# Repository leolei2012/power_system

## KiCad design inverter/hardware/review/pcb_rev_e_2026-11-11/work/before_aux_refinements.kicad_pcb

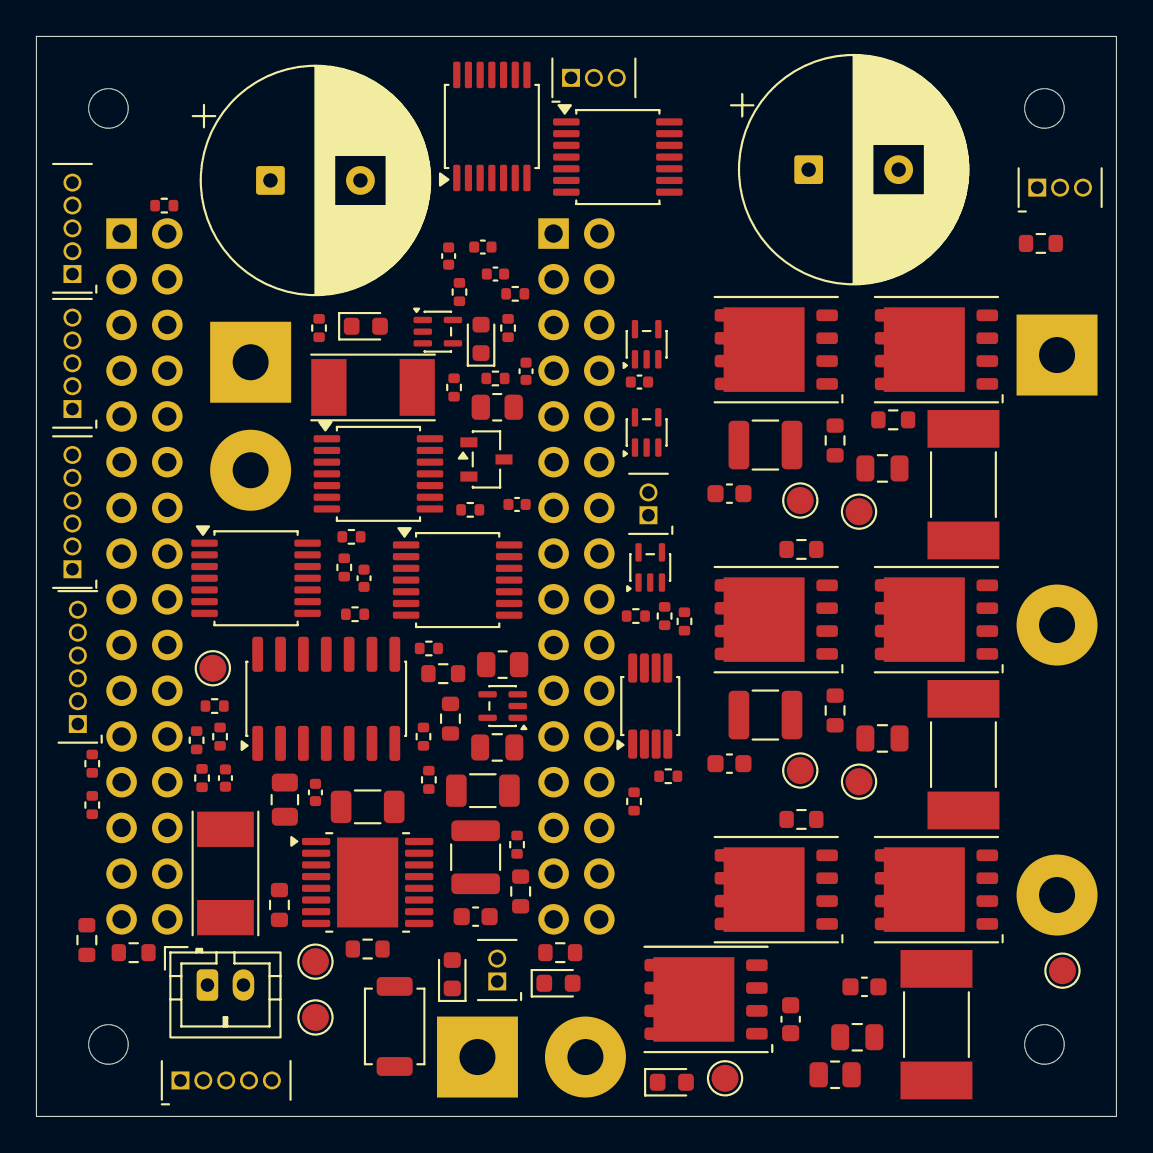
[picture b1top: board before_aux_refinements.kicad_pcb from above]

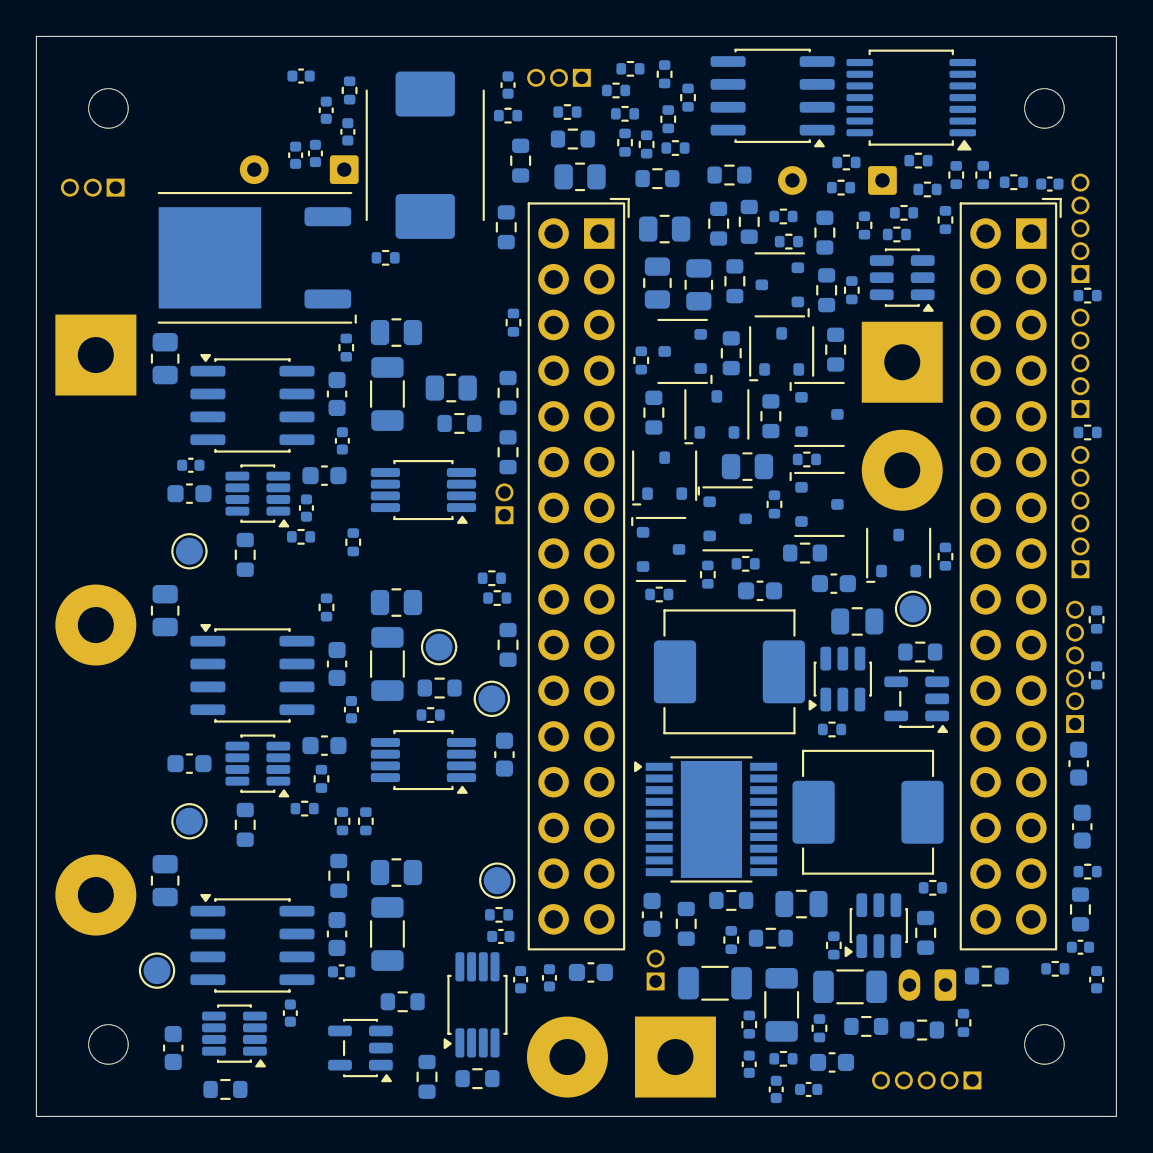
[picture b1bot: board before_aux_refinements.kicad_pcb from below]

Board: 6 copper layers, 60.0 x 60.0 mm, 321 parts (194 on the bottom side), 220 nets, no tracks yet.

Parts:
C1: 1u; C_0805_2012Metric
C2: 22n; C_0603_1608Metric
C3, C6, C11: 10u; C_1206_3216Metric
C4, C5, C9, C12, C24, C26, C28, C30, C32, C34, C36, C37, C38, C39, C51, C52, C53: 100n; C_0603_1608Metric
C7: 470n; C_0805_2012Metric
C8: 22u; C_1210_3225Metric
C10, C27, C31, C35: 4.7u; C_0805_2012Metric
C13, C14: 22u; C_1206_3216Metric
C15, C23: 1u; C_0603_1608Metric
C16: 2.2u; C_0603_1608Metric
C17, C40, C41, C43, C45, C47, C49, C54, C56, C57, C58, C59, C60, C61, C62, C82: 100n; C_0402_1005Metric
C18: 10u; C_0805_2012Metric
C19, C20: 220u / 100V; CP_Radial_D12.5mm_H25mm_P5.00mm
C21, C22: 2.2u / 100V X7R; C_1210_3225Metric
C25, C29, C33: 2.2u; C_1206_3216Metric
C42: 100p; C_0402_1005Metric
C44, C46, C48, C69, C70, C71, C72, C73, C74, C75, C76: 1n; C_0402_1005Metric
C50, C55: 10n; C_0402_1005Metric
D1: MBRD20150CT-13; Diodes_MBRD20150CT_TO252_Recommended
D2: SMCJ60CA / CANDIDATE DNP; SMC_DO-214AB_Bidirectional
D3: PWR; LED_0603_1608Metric
D4: LED_RUN; LED_0603_1608Metric
D5: LED_FAULT; LED_0603_1608Metric
D6: LED_COMM; LED_0603_1608Metric
D7: LED_AUX; LED_0603_1608Metric
D201, D202, D203, D204, D205, D206, D207, D208, D209, D210: BAT54S,215; Nexperia_SOT23_Reflow_Pad0.70x0.60mm
F1: 0476015.MRSN; Littelfuse_NANO2_451_476_Pad1.96x3.15mm_Gap2.95mm
F2: 0451002.MRL; Littelfuse_NANO2_451_476_Pad1.96x3.15mm_Gap2.95mm
H1, H2, H3, H4: MountingHole_2.2mm_M2
J2: AUX: +12..24V / GND; JST_PH_B2B-PH-K_1x02_P2.00mm_Vertical
J3: DC INPUT: + / -; WireSolder_2P_P6.00mm_D2.00mm
J4: RAW PWM: U / V / W; WireSolder_3P_P15.00mm_D2.00mm
J5: BRAKE POWER: BR+ / BR_SW; WireSolder_2P_P6.00mm_D2.00mm
J7: OPTIONAL SENSOR 5V / GND; HCTL_PZ127_1x02_P1.27mm_Drill0.70mm
J8: EXTERNAL 10k NTC; HCTL_PZ127_1x02_P1.27mm_Drill0.70mm
J9: ENC_A: PWR GND A B Z; HCTL_PZ127_1x05_P1.27mm_Drill0.70mm
J10: ENC_B: PWR GND A B Z; HCTL_PZ127_1x05_P1.27mm_Drill0.70mm
J11: SPI_A: PWR GND SCK MOSI MISO CS; HCTL_PZ127_1x06_P1.27mm_Drill0.70mm
J12: SPI_B: PWR GND SCK MOSI MISO CS; HCTL_PZ127_1x06_P1.27mm_Drill0.70mm
J13: SWD: VTREF IO CLK GND NRST; HCTL_PZ127_1x05_P1.27mm_Drill0.70mm
J14: TTL: TX RX GND; HCTL_PZ127_1x03_P1.27mm_Drill0.70mm
J15: CAN: H L GND; HCTL_PZ127_1x03_P1.27mm_Drill0.70mm
J101, J102: PM254V-12-32-H85; XFCN_PM254V-12-32-H85_2x16_P2.54mm_Vertical_Drill1.02mm
L1, L2: 4.7uH; L_Sunlord_MWSA0603S
Q1, Q2, Q3, Q4, Q5, Q6, Q7: BSC110N15NS5; Infineon_BSC110N15NS5_PG-TDSON8_8PhysicalPins
Q8: MMBT3904LT1G; onsemi_SOT-23_CASE318_Recommended
R1: 78.7k; R_0603_1608Metric
R2, R4, R7, R10, R11, R15, R16, R18, R21, R22, R23, R24, R27, R28, R29, R30, R33, R34, R35, R36, R50, R51, R55, R56, R60, R61, R65, R66, R209: 10k; R_0603_1608Metric
R3: 221k; R_0603_1608Metric
R5: 402k; R_0603_1608Metric
R6: 7.87k; R_0603_1608Metric
R8, R9: 100k; R_0603_1608Metric
R12: 20k; R_0603_1608Metric
R13, R40, R41, R44, R45, R70, R72, R73, R74, R76, R77, R78, R79, R80, R81, R82, R95, R97, R99, R102, R104, R106, R112, R118, R125, R128, R143, R160: 10k; R_0402_1005Metric
R14: 49.9k; R_0603_1608Metric
R17, R19, R20, R25, R26, R31, R32: 15; R_0805_2012Metric
R37, R38, R39: 47; R_0603_1608Metric
R42, R47: 39k; R_0402_1005Metric
R43, R46: 1.8k; R_0402_1005Metric
R48, R49, R53, R54, R58, R59, R63, R64: 240k; R_0805_2012Metric
R52, R57, R62, R67: 47; R_0402_1005Metric
R68: 20k; R_0402_1005Metric
R69: 13k; R_0402_1005Metric
R71: 76.1k; R_0402_1005Metric
R75, R83: 100k; R_0402_1005Metric
R84, R85, R86, R87, R88, R89, R90, R91, R94, R96, R98, R101, R103, R105, R124: 100; R_0402_1005Metric
R100, R107, R113, R119, R126, R127: 0; R_0402_1005Metric
R108, R109, R110, R111, R114, R115, R116, R117, R120, R121, R123, R135, R136, R137, R138, R139, R140, R141, R142: 33; R_0402_1005Metric
R129: 120; R_0402_1005Metric
R130, R131, R132, R133, R134: 2.2k; R_0402_1005Metric
R201, R202, R203, R204, R205, R206, R207, R208: 360; R_0603_1608Metric
R210, R211: 1k; R_0603_1608Metric
RS1, RS2, RS3: 5m / 3W / 1%; Milliohm_HoJLR2512_Pad2.1x4.0mm_Gap4.1mm
SW1: AUX_RESET; SW_SPST_TS-1088-xR020
TP1: +12V_DRV; TestPoint_Pad_D1.5mm
TP2: BB_VREG; TestPoint_Pad_D1.5mm
TP3: DRV_PG_LOGIC; TestPoint_Pad_D1.5mm
TP4: SENSOR_PWR_FLT_N; TestPoint_Pad_D1.5mm
TP5: U_PHASE; TestPoint_Pad_D1.5mm
TP6: U_SOURCE; TestPoint_Pad_D1.5mm
TP7: V_PHASE; TestPoint_Pad_D1.5mm
TP8: V_SOURCE; TestPoint_Pad_D1.5mm
TP9: W_PHASE; TestPoint_Pad_D1.5mm
TP10: W_SOURCE; TestPoint_Pad_D1.5mm
TP11: I_U; TestPoint_Pad_D1.5mm
TP12: I_V; TestPoint_Pad_D1.5mm
TP13: I_W; TestPoint_Pad_D1.5mm
TP14: FAULT_LATCH; TestPoint_Pad_D1.5mm
TP16: FAULT_N; TestPoint_Pad_D1.5mm
TP17: ENABLE_IN; TestPoint_Pad_D1.5mm
U1: TPS26600PWPR; HTSSOP-16-1EP_4.4x5mm_P0.65mm_EP3.4x5mm_Mask2.66x2.46mm
U2: TPS55165QPWPRQ1; TI_PWP0020W_HTSSOP-20_4.4x6.5mm_P0.65mm_EP2.79x3.64mm
U3: AP63205WU-7; TSOT-23-6
U4: TPS7A2033PDBVR; SOT-23-5
U5: TPS2553QDBVRQ1; SOT-23-6
U6: TPS3808G33DBVR; SOT-23-6
U7, U8, U9: 2ED2182S06FXUMA1; SOIC-8_3.9x4.9mm_P1.27mm
U10, U11, U12: INA241A1IDDFR; SOT-23-8
U13, U14, U15, U16, U17: TLV9001IDCKR; SOT-353_SC-70-5
U18, U19, U20, U21: TLV3202AIDGK; VSSOP-8_3x3mm_P0.65mm
U22, U23, U24, U25, U26: 74LVC08APW,118; TSSOP-14_4.4x5mm_P0.65mm
U27: 74LVC00APW,118; TSSOP-14_4.4x5mm_P0.65mm
U28: 74LVC74AD,118; SOIC-14_3.9x8.7mm_P1.27mm
U29: UCC27517DBVR; SOT-23-5
U31: SN65HVD232DR; SOIC-8_3.9x4.9mm_P1.27mm

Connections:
+3V3_CORE_REF: D201.2, D202.2, D203.2, D204.2, D205.2, D206.2, D207.2, D208.2, D209.2, D210.2, J13.1, J101.22, J101.32, R143.2
+3V3_INV: C16.1, C17.1, C37.1, C38.1, C39.1, C41.1, C43.1, C45.1, C47.1, C49.1, C51.1, C52.1, C53.1, C54.1, C56.1, C57.1, C58.1, C59.1, C60.1, C61.1, C62.1, C82.1, R7.2, R13.2, R15.2, R40.1, R42.1, R45.1, R68.1, R70.1, R95.2, R97.2, R99.2, R102.2, R104.2, R106.2, R112.2, R118.2, R125.2, R128.2, R130.1, R131.1, R132.1, R133.1, R134.1, U4.5, U6.3, U6.5, U6.6, U10.6, U11.6, U12.6, U13.5, U14.5, U15.5, U16.5, U17.5, U18.8, U19.8, U20.8, U21.8, U22.14, U23.14, U24.14, U25.14, U26.14, U27.14, U28.1, U28.10, U28.13, U28.14, U31.3
+5V_INV: C13.1, C14.1, C15.1, J101.1, J101.3, L2.2, R10.1, U3.1, U4.1, U4.3, U5.1, U5.3
+5V_SENSOR: C18.1, J7.1, R100.1, R107.1, R113.1, R119.1, U5.6
+12V_DRV: C8.1, C9.1, C23.1, C24.1, C27.1, C28.1, C31.1, C32.1, C35.1, C36.1, R71.1, TP1.1, U2.16, U2.17, U7.5, U8.5, U9.5, U29.1
/Analog protection/DRV_UV_DIV: R71.2, R72.1, U21.5
/Auxiliary input/AUX_DVDT: C2.1, U1.12
/Auxiliary input/AUX_FUSED: C1.1, F2.2, R1.1, R3.1, R8.1, U1.1, U1.2
/Auxiliary input/AUX_ILIM: R6.1, U1.11
/Auxiliary input/AUX_IN: F2.1, J2.1
/Auxiliary input/AUX_MODE: R5.1, U1.6
/Auxiliary input/AUX_OV_DIV: R3.2, R4.1, U1.5
/Auxiliary input/AUX_SHDN_N: R8.2, SW1.1, U1.7
/Auxiliary input/AUX_UV_DIV: R1.2, R2.1, U1.3
/Auxiliary input/EFUSE_RTN: C2.2, R2.2, R4.2, R5.2, R6.2, SW1.2, U1.8, U1.17
/Base LEDs/LED_PWR_AN: D3.2, R130.2
/Base interlock/BASE_NOT_READY: U27.8, U27.12, U27.13
/Bus and brake/BR_DRV: R17.1, U29.5
/Bus and brake/BR_GATE: Q7.4, R17.2, R18.1
/Bus and brake/BR_SW: J5.2, Q7.5, Q7.6, Q7.7, Q7.8
/Bus and brake/DC_FUSED: D1.1, D1.3, F1.2
/Bus and brake/DC_INPUT_POS: F1.1, J3.1
/Current sensing/OC_HI_MID: R46.2, R47.1
/Current sensing/OC_LO_MID: R42.2, R43.1
/Current sensing/VBIAS_1V65: U10.3, U10.7, U11.3, U11.7, U12.3, U12.7, U13.3, U13.4
/Current sensing/VBIAS_DIV: C40.1, R40.2, R41.1, U13.1
/Driver supply/BB_BST1: C4.1, U2.3
/Driver supply/BB_BST2: C5.1, U2.19
/Driver supply/BB_L1: C4.2, L1.1, U2.2
/Driver supply/BB_L2: C5.2, L1.2, U2.20
/Driver supply/BB_PG_DLY: R9.1, U2.10
/Driver supply/BB_VREG: C10.1, TP2.1, U2.11, U2.12, U2.14
/Driver supply/DRV_PG_NOM: R10.2, R11.1, U2.15
/Encoders and SPI/ENC_A_A_PORT: J9.3, R94.1
/Encoders and SPI/ENC_A_B_PORT: J9.4, R96.1
/Encoders and SPI/ENC_A_VCC: J9.1, R100.2
/Encoders and SPI/ENC_A_Z_PORT: J9.5, R98.1
/Encoders and SPI/ENC_B_A_PORT: J10.3, R101.1
/Encoders and SPI/ENC_B_B_PORT: J10.4, R103.1
/Encoders and SPI/ENC_B_VCC: J10.1, R107.2
/Encoders and SPI/ENC_B_Z_PORT: J10.5, R105.1
/Encoders and SPI/SPI_A_CS_PORT: J11.6, R111.2
/Encoders and SPI/SPI_A_MISO_PORT: J11.5, R110.2
/Encoders and SPI/SPI_A_MOSI_PORT: J11.4, R109.2
/Encoders and SPI/SPI_A_SCK_PORT: J11.3, R108.2
/Encoders and SPI/SPI_A_VCC: J11.1, R113.2
/Encoders and SPI/SPI_B_CS_PORT: J12.6, R117.2
/Encoders and SPI/SPI_B_MISO_PORT: J12.5, R116.2
/Encoders and SPI/SPI_B_MOSI_PORT: J12.4, R115.2
/Encoders and SPI/SPI_B_SCK_PORT: J12.3, R114.2
/Encoders and SPI/SPI_B_VCC: J12.1, R119.2
/Hardware latch/ENABLE_N: U24.10, U27.3
/Hardware latch/FAULT_ACTIVE: R74.1, U27.6
/Hardware latch/FAULT_BASE: Q8.1, R74.2, R75.1
/Hardware latch/FAULT_LATCH: TP14.1, U28.5
/Hardware latch/HEALTH_ALL: U24.6, U24.9, U24.12, U27.4, U28.4
/Hardware latch/HEALTH_CHAIN_1: U22.3, U22.4
/Hardware latch/HEALTH_CHAIN_2: U22.6, U22.9
/Hardware latch/HEALTH_CHAIN_3: U22.8, U22.12
/Hardware latch/HEALTH_CHAIN_4: U22.11, U23.1
/Hardware latch/HEALTH_CHAIN_5: U23.3, U23.4
/Hardware latch/HEALTH_CHAIN_6: U23.6, U23.9
/Hardware latch/HEALTH_CHAIN_7: U23.8, U23.12
/Hardware latch/HEALTH_CHAIN_8: U23.11, U24.1
/Hardware latch/HEALTH_CHAIN_9: U24.3, U24.4
/Hardware latch/HEALTH_UNLATCHED: U24.11, U25.1
/Hardware latch/NO_LATCH: U24.13, U27.5, U28.6
/Hardware latch/RESET_CLK: C55.1, R73.2, U28.3
/Hardware latch/RESET_REQUEST: R73.1, U24.8
/Logic and sensors/BUCK_BST: C12.1, U3.6
/Logic and sensors/BUCK_SW: C12.2, L2.1, U3.5
/Logic and sensors/SENSOR_ILIM: R14.1, U5.5
/Logic and sensors/SENSOR_PWR_FLT_N: R15.1, TP4.1, U5.4
/SWD UART CAN and status/CAN_H: J15.1, R129.1, U31.7
/SWD UART CAN and status/CAN_L: J15.2, R129.2, U31.6
/SWD UART CAN and status/CAN_RX_PHY: R127.1, U31.4
/SWD UART CAN and status/CAN_TX_PHY: R126.2, R128.1, U31.1
/SWD UART CAN and status/LED_AN_1: D4.2, R131.2
/SWD UART CAN and status/LED_AN_2: D5.2, R132.2
/SWD UART CAN and status/LED_AN_3: D6.2, R133.2
/SWD UART CAN and status/LED_AN_4: D7.2, R134.2
/SWD UART CAN and status/SWCLK_PORT: J13.3, R121.1
/SWD UART CAN and status/SWDIO_PORT: J13.2, R120.1
/SWD UART CAN and status/UART_RX_PORT: J14.2, R124.1
/SWD UART CAN and status/UART_TX_PORT: J14.1, R123.2
/U half bridge/U_BOOT: C25.1, C26.1, U7.8
/U half bridge/U_GATE_H: Q1.4, R19.2, R21.1
/U half bridge/U_GATE_L: Q2.4, R20.2, R22.1
/U half bridge/U_HO: R19.1, U7.7
/U half bridge/U_LO: R20.1, U7.4
/V half bridge/V_BOOT: C29.1, C30.1, U8.8
/V half bridge/V_GATE_H: Q3.4, R25.2, R27.1
/V half bridge/V_GATE_L: Q4.4, R26.2, R28.1
/V half bridge/V_HO: R25.1, U8.7
/V half bridge/V_LO: R26.1, U8.4
/Voltage and NTC/V_DC_DIV: C42.1, R50.2, R51.1, U14.1
/Voltage and NTC/V_DC_DIV1: R48.2, R49.1
/Voltage and NTC/V_DC_DIV2: R49.2, R50.1
/Voltage and NTC/V_U: R57.1, U15.3, U15.4
/Voltage and NTC/V_U_DIV: C44.1, R55.2, R56.1, U15.1
/Voltage and NTC/V_U_DIV1: R53.2, R54.1
/Voltage and NTC/V_U_DIV2: R54.2, R55.1
/Voltage and NTC/V_V: R62.1, U16.3, U16.4
/Voltage and NTC/V_V_DIV: C46.1, R60.2, R61.1, U16.1
/Voltage and NTC/V_V_DIV1: R58.2, R59.1
/Voltage and NTC/V_V_DIV2: R59.2, R60.1
/Voltage and NTC/V_W: R67.1, U17.3, U17.4
/Voltage and NTC/V_W_DIV: C48.1, R65.2, R66.1, U17.1
/Voltage and NTC/V_W_DIV1: R63.2, R64.1
/Voltage and NTC/V_W_DIV2: R64.2, R65.1
/W half bridge/W_BOOT: C33.1, C34.1, U9.8
/W half bridge/W_GATE_H: Q5.4, R31.2, R33.1
/W half bridge/W_GATE_L: Q6.4, R32.2, R34.1
/W half bridge/W_HO: R31.1, U9.7
/W half bridge/W_LO: R32.1, U9.4
AUX_FLT_N: R7.1, U1.14, U24.5
AUX_PROTECTED: C3.1, C6.1, C7.1, C11.1, U1.15, U1.16, U2.4, U2.5, U2.6, U3.2, U3.3
BASE_LOGIC_OK: R13.1, U6.1, U23.13, U27.9
BASE_READY: R210.1, U27.11
BRAKE_IN: R16.1, R142.2, U29.3
BUS_OV_OK: U21.1, U23.5
CTRL_READY: J102.10, R160.1, U26.13
DRIVE_PERMIT: R83.1, U25.3, U25.5, U25.10, U25.13, U26.2, U26.5, U26.10
DRV_PG_LOGIC: R11.2, R12.1, TP3.1, U24.2, U27.10
DRV_UV_OK: U21.7, U23.10
ENABLE_IN: R82.1, R141.2, TP17.1, U26.12
ENABLE_QUALIFIED: U25.2, U26.11, U27.1, U27.2
FAULT_N: Q8.3, R211.1, TP16.1
GND: C1.2, C3.2, C6.2, C7.2, C8.2, C9.2, C10.2, C11.2, C13.2, C14.2, C15.2, C16.2, C17.2, C18.2, C19.2, C20.2, C21.2, C22.2, C23.2, C24.2, C37.2, C38.2, C39.2, C40.2, C41.2, C42.2, C43.2, C44.2, C45.2, C46.2, C47.2, C48.2, C49.2, C50.2, C51.2, C52.2, C53.2, C54.2, C55.2, C56.2, C57.2, C58.2, C59.2, C60.2, C61.2, C62.2, C69.2, C70.2, C71.2, C72.2, C73.2, C74.2, C75.2, C76.2, C82.2, D2.2, D3.1, D201.1, D202.1, D203.1, D204.1, D205.1, D206.1, D207.1, D208.1, D209.1, D210.1, J2.2, J3.2, J7.2, J8.2, J9.2, J10.2, J11.2, J12.2, J13.4, J14.3, J15.3, J101.2, J101.4, J101.21, J101.31, J102.9, J102.27, J102.31, Q7.1, Q7.2, Q7.3, Q8.2, R9.2, R12.2, R14.2, R16.2, R18.2, R41.2, R44.2, R47.2, R51.2, R56.2, R61.2, R66.2, R69.2, R72.2, R75.2, R76.2, R77.2, R78.2, R79.2, R80.2, R81.2, R82.2, R83.2, R160.2, R209.2, RS1.2, RS2.2, RS3.2, U1.9, U2.1, U2.7, U2.8, U2.9, U2.13, U2.18, U2.21, U3.4, U4.2, U5.2, U6.2, U10.1, U10.2, U10.4, U11.1, U11.2, U11.4, U12.1, U12.2, U12.4, U13.2, U14.2, U15.2, U16.2, U17.2, U18.4, U19.4, U20.4, U21.4, U22.7, U23.7, U24.7, U25.7, U26.7, U27.7, U28.2, U28.7, U28.11, U28.12, U29.2, U29.4, U31.2
I_U: R37.1, TP11.1, U10.5, U18.2, U18.5
I_U_PORT: R37.2, R201.1
I_V: R38.1, TP12.1, U11.5, U19.2, U19.5
I_V_PORT: R38.2, R202.1
I_W: R39.1, TP13.1, U12.5, U20.2, U20.5
I_W_PORT: R39.2, R203.1
NRST: J13.5, J102.32
unnamed: D201.3, R84.1, R201.2
unnamed: D202.3, R85.1, R202.2
unnamed: D203.3, R86.1, R203.2
unnamed: D204.3, R87.1, R204.2
unnamed: D205.3, R88.1, R205.2
unnamed: D206.3, R89.1, R206.2
unnamed: D207.3, R90.1, R207.2
unnamed: D208.3, R91.1, R208.2
OC_HIGH_REF: R45.2, R46.1, U18.3, U19.3, U20.3
OC_LOW_REF: R43.2, R44.1, U18.6, U19.6, U20.6
OC_U_HIGH_OK: U18.1, U22.1
OC_U_LOW_OK: U18.7, U22.2
OC_V_HIGH_OK: U19.1, U22.5
OC_V_LOW_OK: U19.7, U22.10
OC_W_HIGH_OK: U20.1, U22.13
OC_W_LOW_OK: U20.7, U23.2
OV_REF_1V30: R68.2, R69.1, U21.3, U21.6
PA0: J101.5, R94.2, R95.1
PA1: J101.6, R96.2, R97.1
PA2: J101.7, R98.2, R99.1
PA3: J101.8, R105.2, R106.1
PA4: C73.1, J101.9, R88.2
PA5: J101.10, R108.1
PA6: J101.11, R110.1
PA7: J101.12, R109.1
PA8: J101.13, R135.1
PA9: J101.14, R137.1
PA10: J101.15, R139.1
PA11: J101.16, R127.2
PA12: J101.17, R126.1
PA13: J101.18, R120.2
PA14: J101.19, R121.2
PA15: J101.20, R111.1, R112.1
PB0: C74.1, J101.23, R89.2
PB1: C75.1, J101.24, R90.2
PB2: C76.1, J101.25, R91.2
PB5: D7.1, J101.28
PB6: J101.29, R101.2, R102.1
PB7: J101.30, R103.2, R104.1
PB10: J102.3, R123.1
PB11: J102.4, R124.2, R125.1
PB12: D210.3, J102.5, R143.1, R211.2
PB13: J102.6, R136.1
PB14: J102.7, R138.1
PB15: J102.8, R140.1
PC0: C69.1, J102.11, R84.2
PC1: C70.1, J102.12, R85.2
PC2: C71.1, J102.13, R86.2
PC3: C72.1, J102.14, R87.2
PC4: J102.15, R141.1
PC5: D4.1, J102.16
PC6: J102.17, R142.1
PC8: D5.1, J102.19
PC9: J102.20, R117.1, R118.1
PC10: J102.21, R114.1
PC11: J102.22, R116.1
PC12: J102.23, R115.1
PC13: D209.3, J102.24, R209.1, R210.2
PD2: D6.1, J102.28
PWM_UH_IN: R76.1, R135.2, U25.4
PWM_UL_IN: R77.1, R136.2, U25.9
PWM_VH_IN: R78.1, R137.2, U25.12
PWM_VL_IN: R79.1, R138.2, U26.1
PWM_WH_IN: R80.1, R139.2, U26.4
PWM_WL_IN: R81.1, R140.2, U26.9
TEMP_NTC: C50.1, J8.1, R70.2, R208.1
U_HIN: R23.1, U7.1, U25.6
U_LIN: R24.1, U7.2, U25.8
U_PHASE: C25.2, C26.2, J4.1, Q1.1, Q1.2, Q1.3, Q2.5, Q2.6, Q2.7, Q2.8, R21.2, R53.1, TP5.1, U7.6
U_SOURCE: C27.2, C28.2, Q2.1, Q2.2, Q2.3, R22.2, R23.2, R24.2, RS1.1, TP6.1, U7.3, U10.8
VBUS: C19.1, C20.1, C21.1, C22.1, D1.2, D2.1, J5.1, Q1.5, Q1.6, Q1.7, Q1.8, Q3.5, Q3.6, Q3.7, Q3.8, Q5.5, Q5.6, Q5.7, Q5.8, R48.1
V_DC: R52.1, U14.3, U14.4, U21.2
V_DC_PORT: R52.2, R204.1
V_HIN: R29.1, U8.1, U25.11
V_LIN: R30.1, U8.2, U26.3
V_PHASE: C29.2, C30.2, J4.2, Q3.1, Q3.2, Q3.3, Q4.5, Q4.6, Q4.7, Q4.8, R27.2, R58.1, TP7.1, U8.6
V_SOURCE: C31.2, C32.2, Q4.1, Q4.2, Q4.3, R28.2, R29.2, R30.2, RS2.1, TP8.1, U8.3, U11.8
V_U_PORT: R57.2, R205.1
V_V_PORT: R62.2, R206.1
V_W_PORT: R67.2, R207.1
W_HIN: R35.1, U9.1, U26.6
W_LIN: R36.1, U9.2, U26.8
W_PHASE: C33.2, C34.2, J4.3, Q5.1, Q5.2, Q5.3, Q6.5, Q6.6, Q6.7, Q6.8, R33.2, R63.1, TP9.1, U9.6
W_SOURCE: C35.2, C36.2, Q6.1, Q6.2, Q6.3, R34.2, R35.2, R36.2, RS3.1, TP10.1, U9.3, U12.8

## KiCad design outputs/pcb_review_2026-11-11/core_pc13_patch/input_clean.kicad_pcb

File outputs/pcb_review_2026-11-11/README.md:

# Rev E 两板 PCB 独立审查

运行方式：在仓库根目录使用 KiCad 自带 Python 执行 `tools/verify_reve_pcbs.py`。工具只读取已保存 PCB、当前 XML 和两个合同；只在本目录写报告，不保存 PCB 或工程。默认重新运行两板原生 CLI DRC，报告实际违规、未连接和原理图一致性数量；`--skip-drc` 仅用于局部读回，不能作为最终 DRC 结果。

最终检查输入为 `docs/pcb_stack_contract_rev_e.json`、`docs/daughterboard_pin_contract.json` 及两块板各自的 `review/*.net.xml`。原理图共 364 个电气位号、1202 个唯一物理引脚；每板另加 H1–H4 安装孔。MOS 大散热铜面重复 5 号，因此实际铜焊盘数量与唯一物理引脚数量分别记录。

检查内容：

- 电气位号、全部物理 pad、原理图网络及完整网分区、DNP、封装和数值。显式 NC 仍须保留实体 pad，可使用空 PCB 网络；同号重复铜 pad 分别核网。
- 60×60 mm 外框、板厚、4/6 层、四孔同心、2.2 mm NPTH 及孔心半径 2.8 mm 铜净空。未填充铜区会单独列出，不能由空缓存证明净空。
- J101/J102 的 64 个同号 pad 在共同 XY 中逐个同心。公头在核心 TOP，母座在底板 BOTTOM；供电网络按合同别名检查，底板闲置触点按 NC 检查。
- 原生 courtyard 多边形的同面交叠、越板、缺失，以及安装硬件区域和下板按键操作区的障碍。
- MCU、RESET/BOOT 的顶面要求和按键近边位置；全部已关联 3D 模型路径解析。缺模型、通用模型和实际高度不能相互替代。
- 对当前 PCB 重跑的原生 DRC 和 pcbnew 原始未连接数；报告记录输入哈希，并核对审查前后源文件未变。

已核机械基础：PZ254V-12-32P 公塑座名义 40.64×5.0 mm，PM254V-12-32-H85 母塑座 41.14×5.0 mm；38.10 mm 只是首末针中心距。详见共享库 `docs/parts/batch_2026-11-10/README.md`。TS-1101-C-W 按键本体 6.05×3.70 mm、顶高 2.50±0.10 mm，详见共享库 `docs/parts/TS-1101-C-W.md`。

对当前专用母座封装，在内存 BOARD 内放置后执行 `Flip(position, False)`，实际同号 pad 与 0°公头对齐；KiCad 会显示 B.Cu / 180°。应以实际 pad 坐标验收，不能翻面后再次设 0°。本检查不调用翻面或修改接口。

板间支柱长度、插合深度、按键侧面手指/工具可达性仍按共同合同留待装配核验。塑高 2.5+8.5 mm 不能单独作为已验证的支柱规格。本目录的检查结果是设计审查记录。

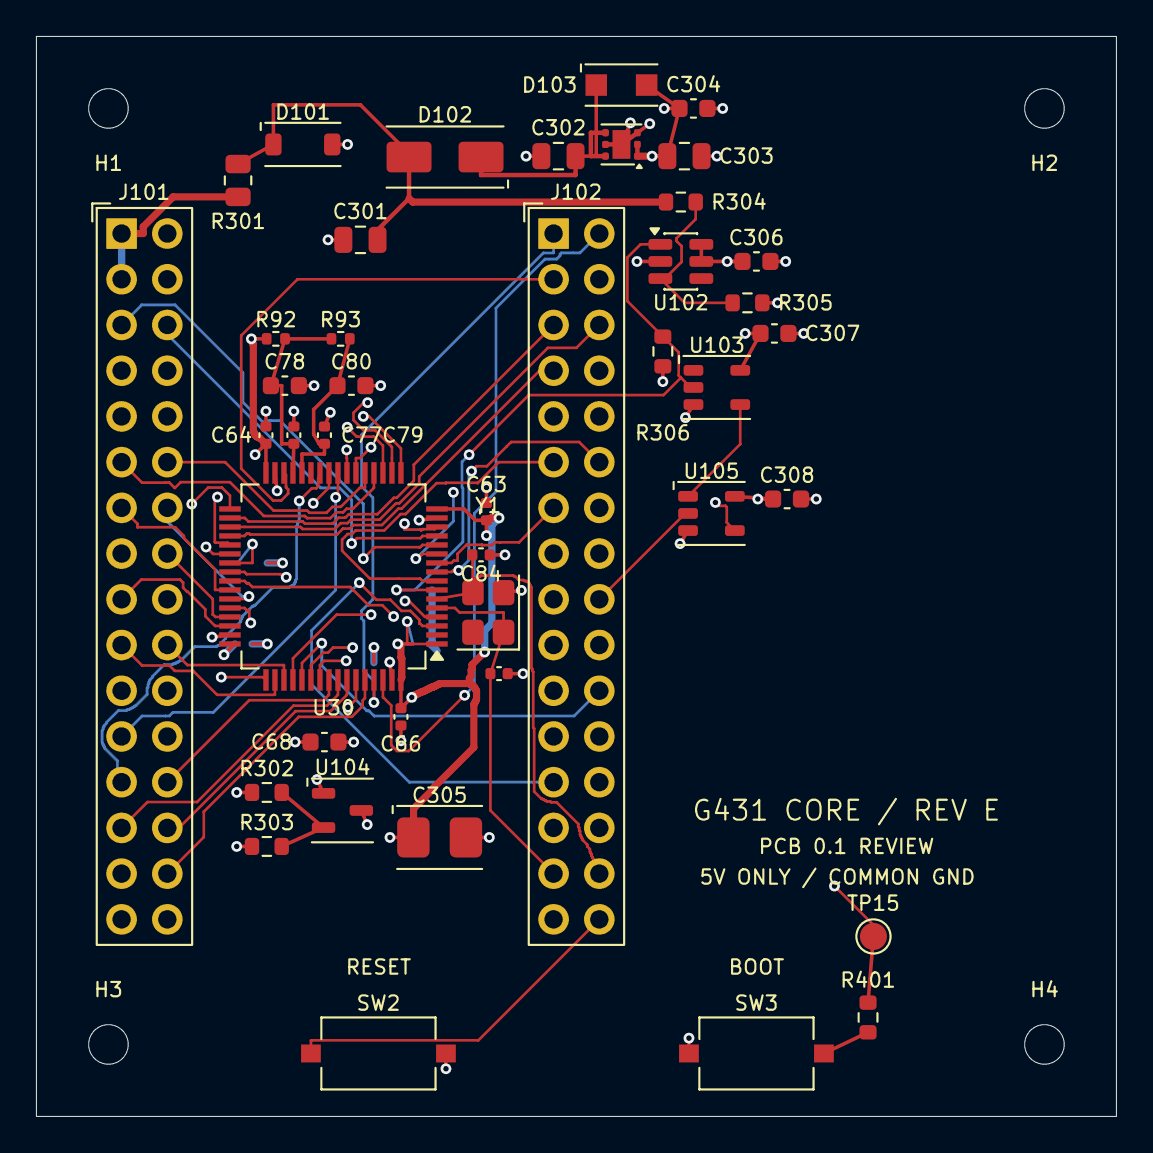
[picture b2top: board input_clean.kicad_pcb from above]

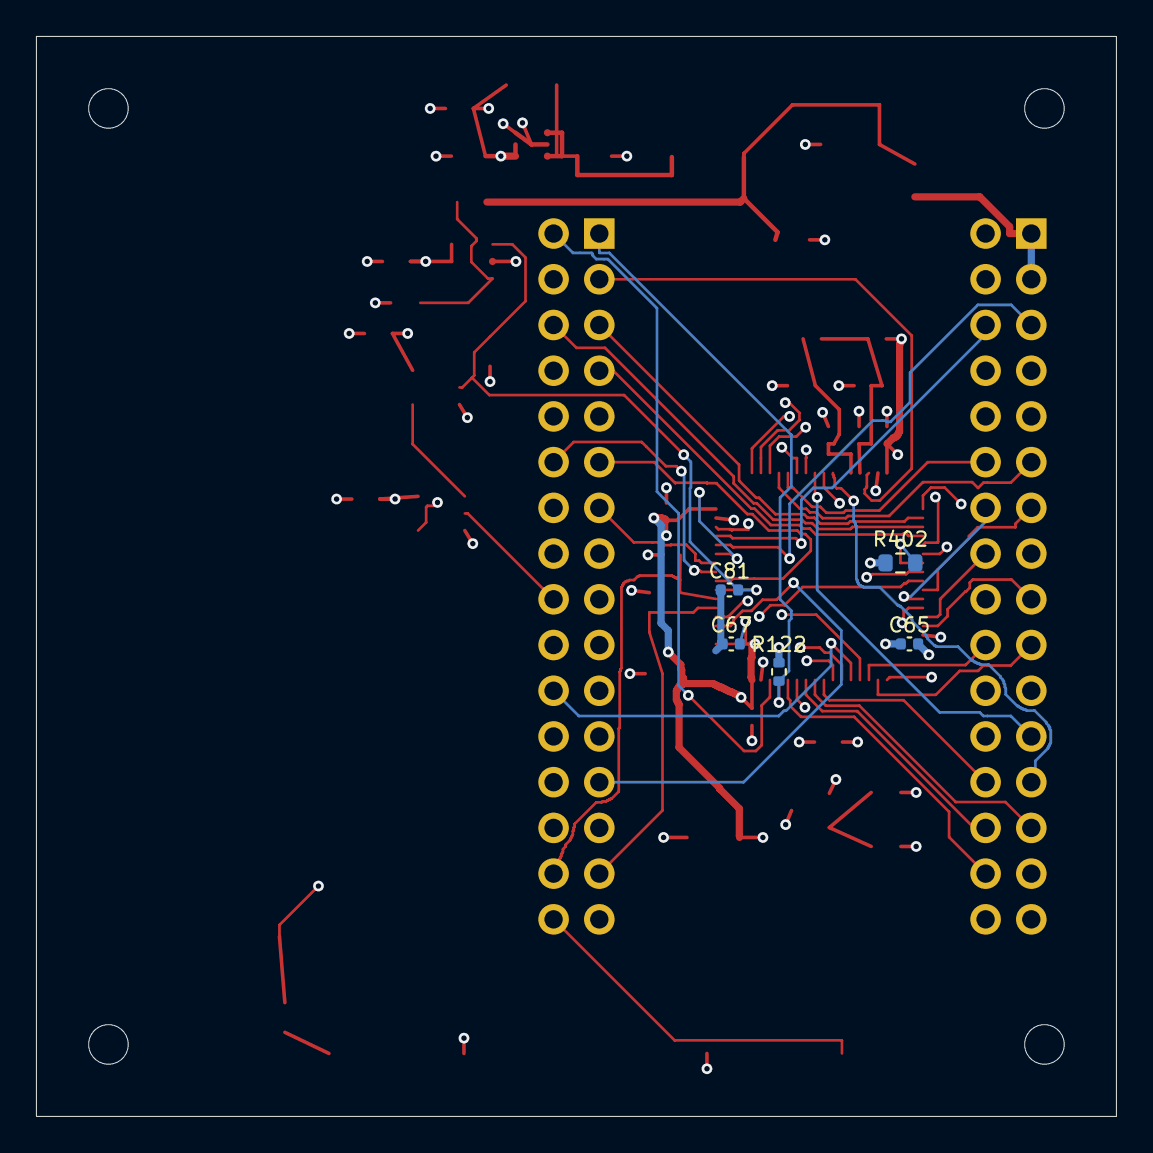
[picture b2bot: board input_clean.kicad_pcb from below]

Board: 4 copper layers, 60.0 x 60.0 mm, 51 parts (5 on the bottom side), 64 nets.

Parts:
C63, C64, C65, C66, C67, C77, C79, C81: 100n; C_0402_1005Metric
C68: 4.7u; C_0603_1608Metric
C78, C80: 1u; C_0603_1608Metric
C83, C84: 18p / provisional; C_0402_1005Metric
C301, C302, C303: 4.7u; C_0805_2012Metric
C304, C306, C307, C308: 100n; C_0603_1608Metric
C305: 47u 10% 10V; KEMET_T491_B_3528_Pad1.80x2.23mm_Gap1.12mm
D101: SMF6.0A-TP; MCC_SOD-123FL_Pad0.91x1.22mm_Gap2.36mm
D102: S1A-13-F; Diodes_SMA_Pad2.50x1.70mm_P4.00mm
D103: PMEG2010ER,115; Nexperia_CFP3_SOD123W_Reflow
H1, H2, H3, H4: M2 NPTH 2.2mm; MountingHole_2.2mm_M2
J101, J102: PZ254V-12-32P; XFCN_PZ254V-12-32P_2x16_P2.54mm_Vertical_Drill1.02mm
R92, R93: 0; R_0402_1005Metric
R122: 10k; R_0402_1005Metric
R301: 0.47; R_0805_2012Metric
R302: 3.83k 0.1%; R_0603_1608Metric
R303: 10k 0.1%; R_0603_1608Metric
R304, R401: 1k; R_0603_1608Metric
R305: 1.1k; R_0603_1608Metric
R306, R402: 10k; R_0603_1608Metric
SW2: MCU_RESET; XKB_TS-1101-C-W_6.05x3.70mm_Pad1.10x1.00mm
SW3: BOOT; XKB_TS-1101-C-W_6.05x3.70mm_Pad1.10x1.00mm
TP15: BOOT0; TestPoint_Pad_D1.5mm
U30: STM32G431RBT6; ST_LQFP-64_10x10mm_P0.5mm_Pad1.2x0.3mm
U101: TLV76733DRVR; WSON-6-1EP_2x2mm_P0.65mm_EP1x1.6mm
U102: TPS3808G33DBVR; SOT-23-6
U103: SN74LVC1G17DBVR; TI_DBV0005A_Pad1.10x0.60mm_P2.60mm
U104: TL431BIDBZR; TI_DBZ0003A_Pad1.30x0.60mm_P2.10mm
U105: SN74LVC1G08DBVR; TI_DBV0005A_Pad1.10x0.60mm_P2.60mm
Y1: 8MHz / CL TBD / DNP; Crystal_SMD_3225-4Pin_3.2x2.5mm

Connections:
+3V3_A_MCU: C77.1, C78.1, R92.2, R93.1, U30.29
+3V3_MCU: C63.1, C64.1, C65.1, C66.1, C67.1, C68.1, C303.1, C304.1, C305.1, C306.1, C307.1, C308.1, D103.2, J101.22, J101.32, R92.1, R302.1, R306.1, SW3.1, U30.1, U30.16, U30.32, U30.48, U30.64, U101.1, U101.2, U102.5, U102.6, U103.5, U104.1, U105.5
+5V_CORE_IN: J101.1, J101.3, R301.1
/Local power and reset/CORE_5V_TVS: C301.1, D101.1, D102.2, R301.2, R304.1
/Local power and reset/CORE_LDO_IN: C302.1, D102.1, D103.1, U101.4, U101.6
/Local power and reset/CORE_MR_5V_PRESENT: R304.2, R305.1, U102.3
/Local power and reset/CORE_SHUNT_REF: R302.2, R303.1, U104.2
CORE_RESET_OK: U103.4, U105.1
CTRL_READY: J102.10, U105.4
GND: C63.2, C64.2, C65.2, C66.2, C67.2, C68.2, C77.2, C78.2, C79.2, C80.2, C81.2, C83.2, C84.2, C301.2, C302.2, C303.2, C304.2, C305.2, C306.2, C307.2, C308.2, D101.2, J101.2, J101.4, J101.21, J101.31, J102.9, J102.27, J102.31, R122.2, R303.2, R305.2, R402.2, SW2.2, U30.15, U30.27, U30.31, U30.47, U30.63, U101.3, U101.5, U101.7, U102.2, U103.3, U104.3, U105.3, Y1.2, Y1.4
HSE_IN: C83.1, J102.29, U30.5, Y1.1
HSE_OUT: C84.1, J102.30, U30.6, Y1.3
NRST: C81.1, J102.32, R306.2, SW2.1, U30.7, U102.1, U103.2
unnamed: R401.1, SW3.2
PA0: J101.5, U30.12
PA1: J101.6, U30.13
PA2: J101.7, U30.14
PA3: J101.8, U30.17
PA4: J101.9, U30.18
PA5: J101.10, U30.19
PA6: J101.11, U30.20
PA7: J101.12, U30.21
PA8: J101.13, U30.42
PA9: J101.14, U30.43
PA10: J101.15, U30.44
PA11: J101.16, U30.45
PA12: J101.17, U30.46
PA13: J101.18, U30.49
PA14: J101.19, U30.50
PA15: J101.20, U30.51
PB0: J101.23, U30.24
PB1: J101.24, U30.25
PB2: J101.25, U30.26
PB3: J101.26, U30.56
PB4: J101.27, U30.57
PB5: J101.28, U30.58
PB6: J101.29, U30.59
PB7: J101.30, U30.60
PB8_BOOT0: J102.1, R122.1, R401.2, TP15.1, U30.61
PB9: J102.2, U30.62
PB10: J102.3, U30.30
PB11: J102.4, U30.33
PB12: J102.5, U30.34
PB13: J102.6, U30.35
PB14: J102.7, U30.36
PB15: J102.8, U30.37
PC0: J102.11, U30.8
PC1: J102.12, U30.9
PC2: J102.13, U30.10
PC3: J102.14, U30.11
PC4: J102.15, U30.22
PC5: J102.16, U30.23
PC6: J102.17, U30.38
PC7: J102.18, R402.1, U30.39, U105.2
PC8: J102.19, U30.40
PC9: J102.20, U30.41
PC10: J102.21, U30.52
PC11: J102.22, U30.53
PC12: J102.23, U30.54
PC13: J102.24, U30.2
PC14: J102.25, U30.3
PC15: J102.26, U30.4
PD2: J102.28, U30.55
VREF_MCU: C79.1, C80.1, R93.2, U30.28
